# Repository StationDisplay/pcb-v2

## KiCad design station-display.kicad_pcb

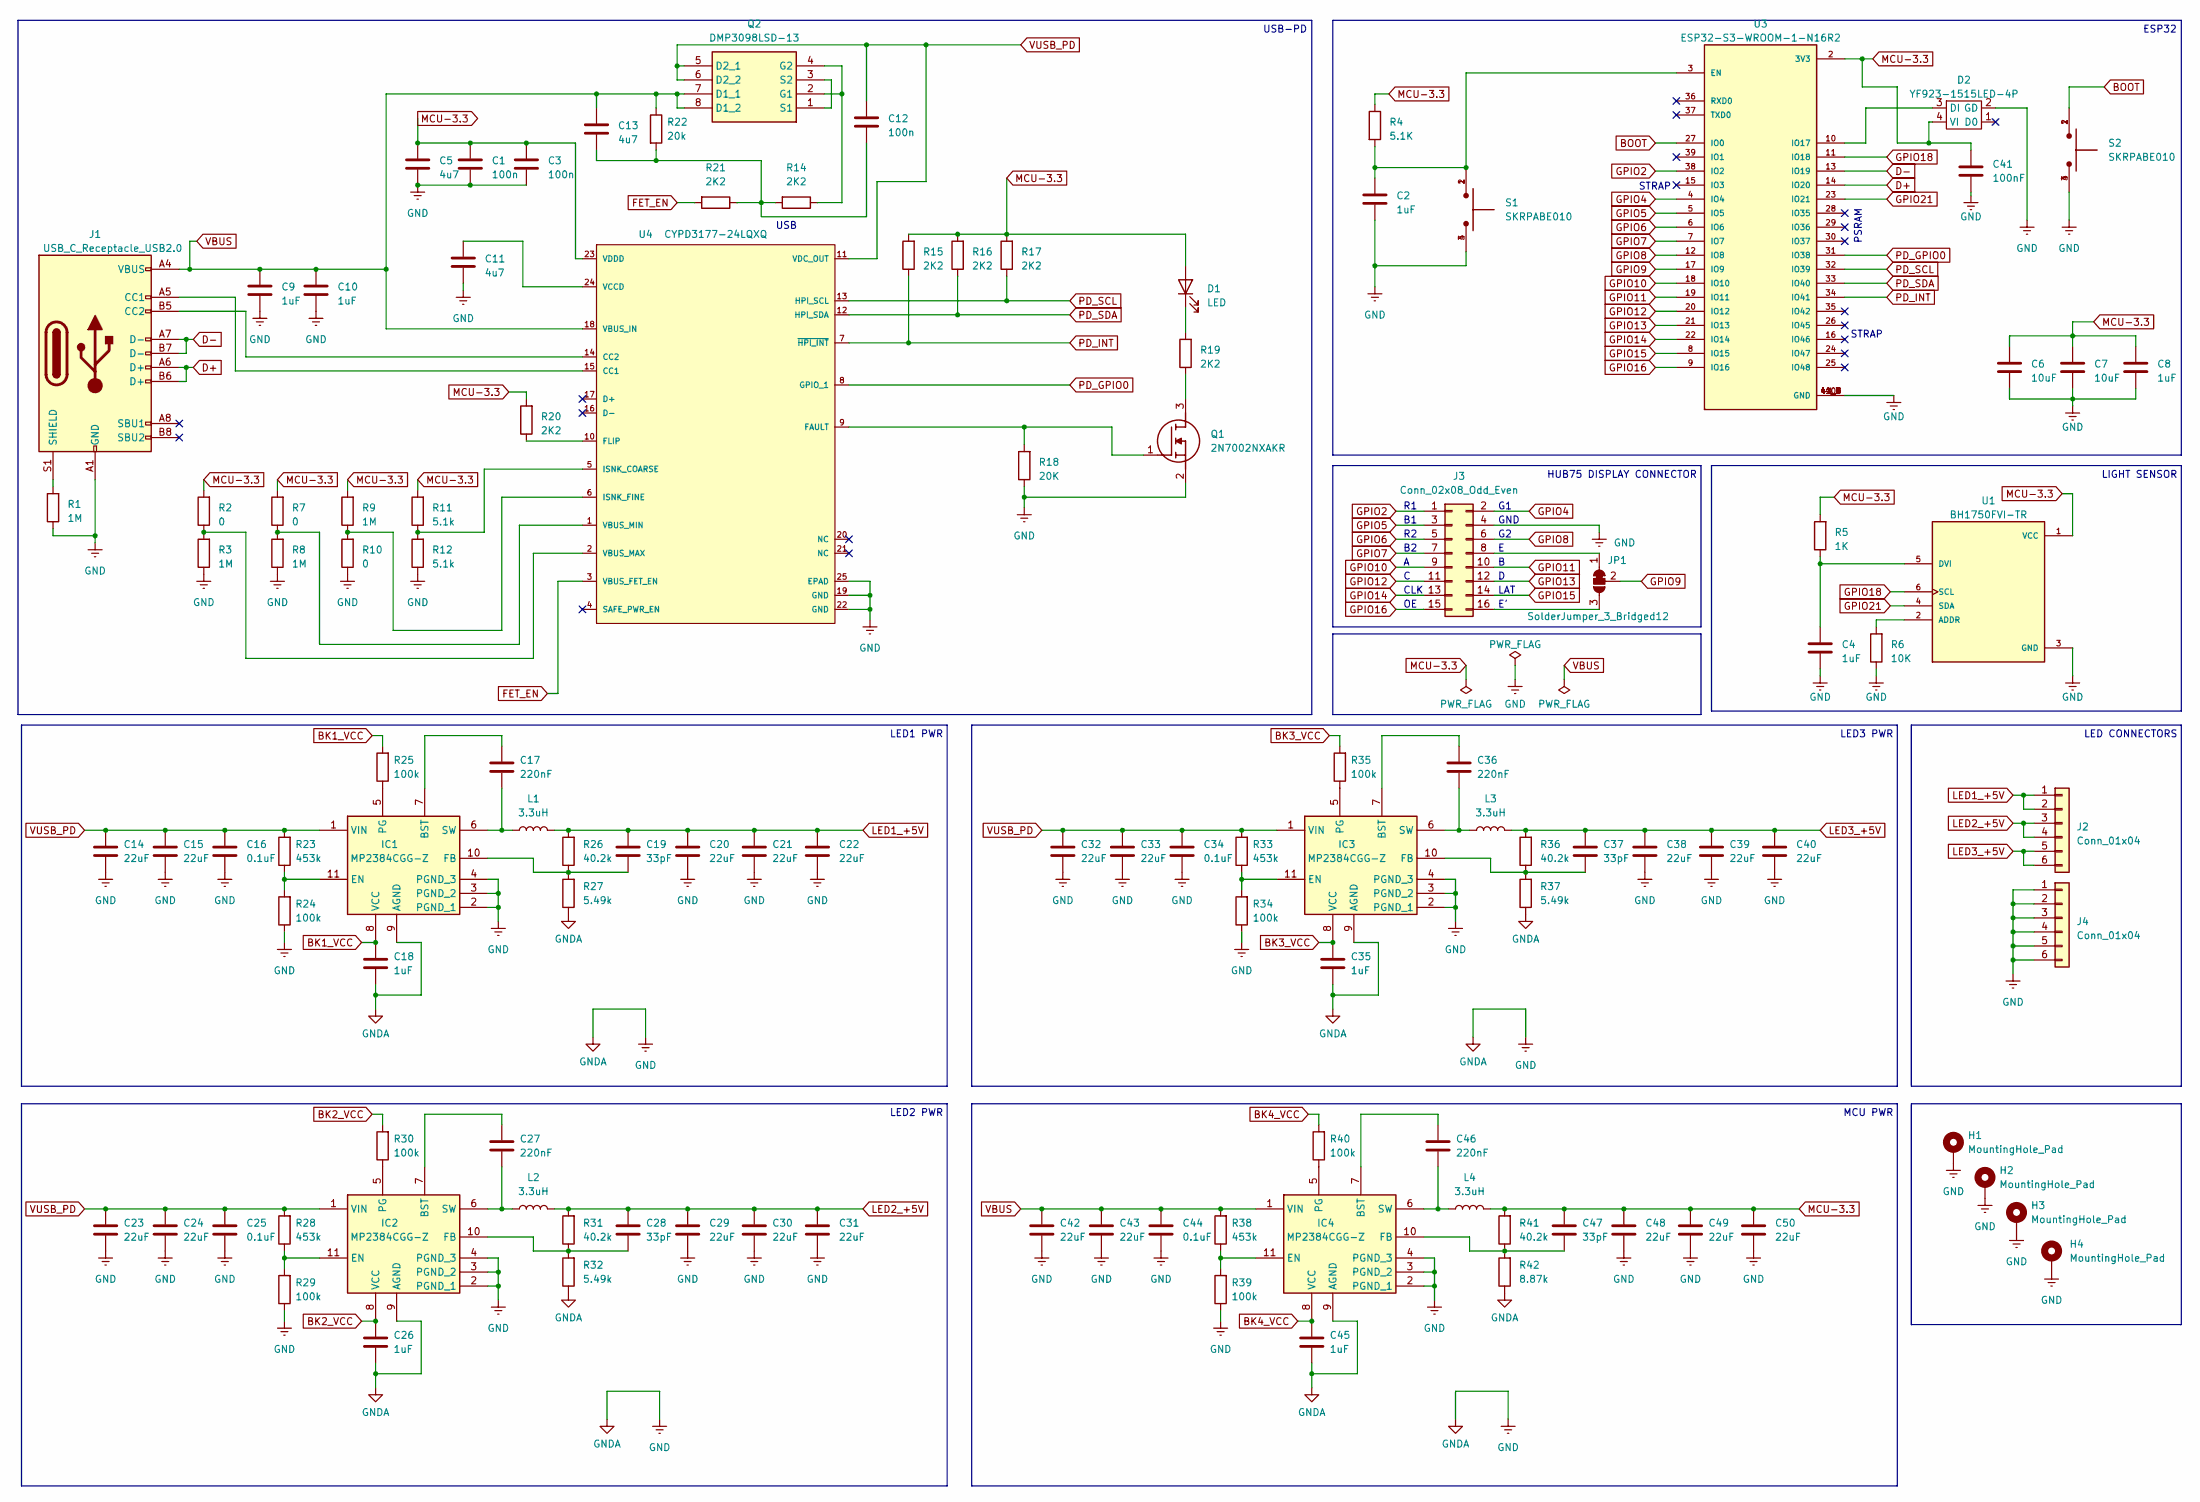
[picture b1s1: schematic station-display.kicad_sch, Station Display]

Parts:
C1, C3, C12: 100n; C_0805_2012Metric
C2, C4, C8, C9, C10: 1uF; C_0805_2012Metric
C5, C11, C13: 4u7; C_0805_2012Metric
C6, C7: 10uF; C_0805_2012Metric
C14, C15, C20, C21, C22, C23, C24, C29, C30, C31, C32, C33, C38, C39, C40, C42, C43, C48, C49, C50: 22uF; C_0805_2012Metric
C16, C25, C34, C44: 0.1uF; C_0805_2012Metric
C17, C27, C36, C46: 220nF; C_0201_0603Metric
C18, C26, C35, C45: 1uF; C_0402_1005Metric
C19, C28, C37, C47: 33pF; C_0805_2012Metric
C41: 100nF; C_0805_2012Metric
D1: LED; LED_0402_1005Metric
D2: YF923-1515LED-4P; LED_SK6812_EC15_1.5x1.5mm; LCSC C5349954
H1, H2, H3, H4: MountingHole_Pad; MountingHole_3.2mm_M3_DIN965_Pad
IC1, IC2, IC3, IC4: MP2384CGG-Z; MP2384CGGZ; Mouser Part Number 946-MP2384CGG-Z
J1: USB_C_Receptacle_USB2.0; TYPE-C-31-M-14; LCSC C223907
J2, J4: Conn_01x04; JST_VH_B6P-VH-B_1x06_P3.96mm_Vertical; LCSC C160314
J3: Conn_02x08_Odd_Even; IDC-Header_2x08_P2.54mm_Vertical_SMD; LCSC C601969
JP1: SolderJumper_3_Bridged12; SolderJumper-3_P1.3mm_Bridged12_RoundedPad1.0x1.5mm
L1, L2, L3, L4: 3.3uH; L_Sunlord_MWSA0605S
Q1: 2N7002NXAKR; SOT95P230X110-3N; Mouser Part Number 771-2N7002NXAKR
Q2: DMP3098LSD-13; SOIC127P600X175-8N; Mouser Part Number 621-DMP3098LSD-13
R1, R3, R8, R9: 1M; R_0402_1005Metric
R2, R7, R10: 0; R_0402_1005Metric
R4: 5.1K; R_0402_1005Metric
R5: 1K; R_0402_1005Metric
R6: 10K; R_0402_1005Metric
R11, R12: 5.1k; R_0402_1005Metric
R14, R15, R16, R17, R19, R20, R21: 2K2; R_0402_1005Metric
R18: 20K; R_0402_1005Metric
R22: 20k; R_0402_1005Metric
R23, R28, R33, R38: 453k; R_0402_1005Metric
R24, R25, R29, R30, R34, R35, R39, R40: 100k; R_0402_1005Metric
R26, R31, R36, R41: 40.2k; R_0402_1005Metric
R27, R32, R37: 5.49k; R_0402_1005Metric
R42: 8.87k; R_0402_1005Metric
S1, S2: SKRPABE010; SW_SKRPABE010
U1: BH1750FVI-TR; XDCR_BH1750FVI-TR; PARTREV D; LCSC C78960
U3: ESP32-S3-WROOM-1-N16R2; XCVR_ESP32-S3-WROOM-1-N16R2; PARTREV v1.0; LCSC C2913198
U4: CYPD3177-24LQXQ; Cypress_Semiconductor-002-16934-0-C-IPC_C; mouser part number 727-CYPD3177-24LQXQ; digikey description IC USB TYPE-C PORT CONTROL 24QFN

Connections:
BK1_VCC: C18.1, IC1.8 (VCC), R25.2
BK2_VCC: C26.1, IC2.8 (VCC), R30.2
BK3_VCC: C35.1, IC3.8 (VCC), R35.2
BK4_VCC: C45.1, IC4.8 (VCC), R40.2
BOOT: S2.1, S2.2, U3.27 (IO0)
D+: J1.A6 (D+), J1.B6 (D+), U3.14 (IO20)
D-: J1.A7 (D-), J1.B7 (D-), U3.13 (IO19)
FET_EN: R21.2, U4.3 (VBUS_FET_EN)
GNDA: C1.2, C2.2, C3.2, C4.2, C5.2, C6.2, C7.2, C8.2, C9.2, C10.2, C11.2, C14.2, C15.2, C16.2, C18.2, C20.2, C21.2, C22.2, C23.2, C24.2, C25.2, C26.2, C29.2, C30.2, C31.2, C32.2, C33.2, C34.2, C35.2, C38.2, C39.2, C40.2, C41.2, C42.2, C43.2, C44.2, C45.2, C48.2, C49.2, C50.2, D2.2 (GD), H1.1, H2.1, H3.1, H4.1, IC1.2 (PGND_1), IC1.3 (PGND_2), IC1.4 (PGND_3), IC1.9 (AGND), IC2.2 (PGND_1), IC2.3 (PGND_2), IC2.4 (PGND_3), IC2.9 (AGND), IC3.2 (PGND_1), IC3.3 (PGND_2), IC3.4 (PGND_3), IC3.9 (AGND), IC4.2 (PGND_1), IC4.3 (PGND_2), IC4.4 (PGND_3), IC4.9 (AGND), J1.A1 (GND), J1.A12 (GND), J1.B1 (GND), J1.B12 (GND), J3.4, J4.1, J4.2, J4.3, J4.4, J4.5, J4.6, Q1.2 (S), R1.1, R3.1, R6.1, R8.1, R10.1, R12.1, R18.1, R24.1, R27.1, R29.1, R32.1, R34.1, R37.1, R39.1, R42.1, S1.3, S1.4, S2.3, S2.4, U1.3 (GND), U3.1 (GND), U3.40 (GND), U3.41_1 (GND), U3.41_2 (GND), U3.41_3 (GND), U3.41_4 (GND), U3.41_5 (GND), U3.41_6 (GND), U3.41_7 (GND), U3.41_8 (GND), U3.41_9 (GND), U4.19 (GND), U4.22 (GND), U4.25 (EPAD)
GPIO2: J3.1, U3.38 (IO2)
GPIO4: J3.2, U3.4 (IO4)
GPIO5: J3.3, U3.5 (IO5)
GPIO6: J3.5, U3.6 (IO6)
GPIO7: J3.7, U3.7 (IO7)
GPIO8: J3.6, U3.12 (IO8)
GPIO9: JP1.2 (C), U3.17 (IO9); also elsewhere on the board
GPIO10: J3.9, U3.18 (IO10)
GPIO11: J3.10, U3.19 (IO11)
GPIO12: J3.11, U3.20 (IO12)
GPIO13: J3.12, U3.21 (IO13)
GPIO14: J3.13, U3.22 (IO14)
GPIO15: J3.14, U3.8 (IO15)
GPIO16: J3.15, U3.9 (IO16)
GPIO18: U1.6 (SCL), U3.11 (IO18)
GPIO21: U1.4 (SDA), U3.23 (IO21)
LED1_+5V: C19.1, C20.1, C21.1, C22.1, J2.1, J2.2, L1.2, R26.2
LED2_+5V: C28.1, C29.1, C30.1, C31.1, J2.3, J2.4, L2.2, R31.2
LED3_+5V: C37.1, C38.1, C39.1, C40.1, J2.5, J2.6, L3.2, R36.2
MCU-3.3: C1.1, C3.1, C5.1, C6.1, C7.1, C8.1, C41.1, C47.1, C48.1, C49.1, C50.1, D1.2 (A), D2.4 (VI), L4.2, R2.2, R4.1, R5.2, R7.2, R9.2, R11.2, R15.2, R16.2, R17.2, R20.2, R41.2, U1.1 (VCC), U3.2 (3V3), U4.23 (VDDD)
unnamed: C12.2, C13.2, R14.2, R21.1, R22.2
unnamed: D1.1 (K), R19.2
unnamed: D2.3 (DI), U3.10 (IO17)
unnamed: C17.1, IC1.7 (BST)
unnamed: IC1.11 (EN), R23.1, R24.2
unnamed: C19.2, IC1.10 (FB), R26.1, R27.2
unnamed: IC1.5 (PG), R25.1
unnamed: C17.2, IC1.6 (SW), L1.1
unnamed: C27.1, IC2.7 (BST)
unnamed: IC2.11 (EN), R28.1, R29.2
unnamed: C28.2, IC2.10 (FB), R31.1, R32.2
unnamed: IC2.5 (PG), R30.1
unnamed: C27.2, IC2.6 (SW), L2.1
unnamed: C36.1, IC3.7 (BST)
unnamed: IC3.11 (EN), R33.1, R34.2
unnamed: C37.2, IC3.10 (FB), R36.1, R37.2
unnamed: IC3.5 (PG), R35.1
unnamed: C36.2, IC3.6 (SW), L3.1
unnamed: C46.1, IC4.7 (BST)
unnamed: IC4.11 (EN), R38.1, R39.2
unnamed: C47.2, IC4.10 (FB), R41.1, R42.2
unnamed: IC4.5 (PG), R40.1
unnamed: C46.2, IC4.6 (SW), L4.1
unnamed: J1.A5 (CC1), U4.15 (CC1)
unnamed: J1.B5 (CC2), U4.14 (CC2)
unnamed: J1.S1 (SHIELD), R1.2
unnamed 55: J3.8, JP1.1 (A); also elsewhere on the board
unnamed 56: J3.16, JP1.3 (B); also elsewhere on the board
unnamed: Q1.3 (D), R19.1
unnamed: Q1.1 (G), R18.2, U4.9 (FAULT)
unnamed: Q2.2 (G1), Q2.4 (G2), R14.1
unnamed: Q2.1 (S1), Q2.3 (S2)
unnamed: R6.2, U1.2 (ADDR)
unnamed: C4.1, R5.1, U1.5 (DVI)
unnamed: C2.1, R4.2, S1.1, S1.2, U3.3 (EN)
unnamed: R20.1, U4.10 (FLIP)
unnamed: R11.1, R12.2, U4.5 (ISNK_COARSE)
unnamed: R9.1, R10.2, U4.6 (ISNK_FINE)
unnamed: R2.1, R3.2, U4.2 (VBUS_MAX)
unnamed: R7.1, R8.2, U4.1 (VBUS_MIN)
unnamed: C11.1, U4.24 (VCCD)
PD_GPIO0: U3.31 (IO38), U4.8 (GPIO_1)
PD_INT: R15.1, U3.34 (IO41), U4.7 (~HPI_INT)
PD_SCL: R17.1, U3.32 (IO39), U4.13 (HPI_SCL)
PD_SDA: R16.1, U3.33 (IO40), U4.12 (HPI_SDA)
VBUS: C9.1, C10.1, C13.1, C42.1, C43.1, C44.1, IC4.1 (VIN), J1.A4 (VBUS), J1.A9 (VBUS), J1.B4 (VBUS), J1.B9 (VBUS), Q2.7 (D1_1), Q2.8 (D1_2), R22.1, R38.2, U4.18 (VBUS_IN)
VUSB_PD: C12.1, C14.1, C15.1, C16.1, C23.1, C24.1, C25.1, C32.1, C33.1, C34.1, IC1.1 (VIN), IC2.1 (VIN), IC3.1 (VIN), Q2.5 (D2_1), Q2.6 (D2_2), R23.2, R28.2, R33.2, U4.11 (VDC_OUT)

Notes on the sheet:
CLK
USB
HUB75 DISPLAY CONNECTOR
MCU PWR
LED1 PWR
STRAP
ESP32
LED CONNECTORS
USB-PD
PSRAM
LED3 PWR
GND
LAT
LIGHT SENSOR
LED2 PWR

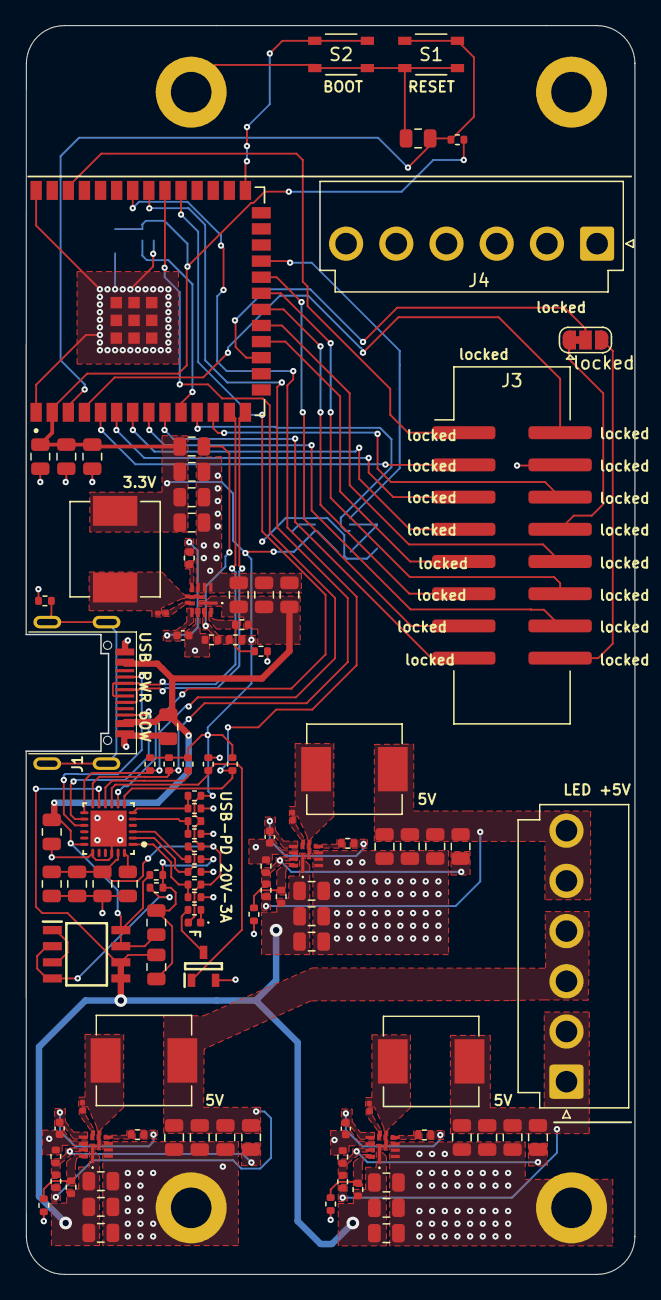
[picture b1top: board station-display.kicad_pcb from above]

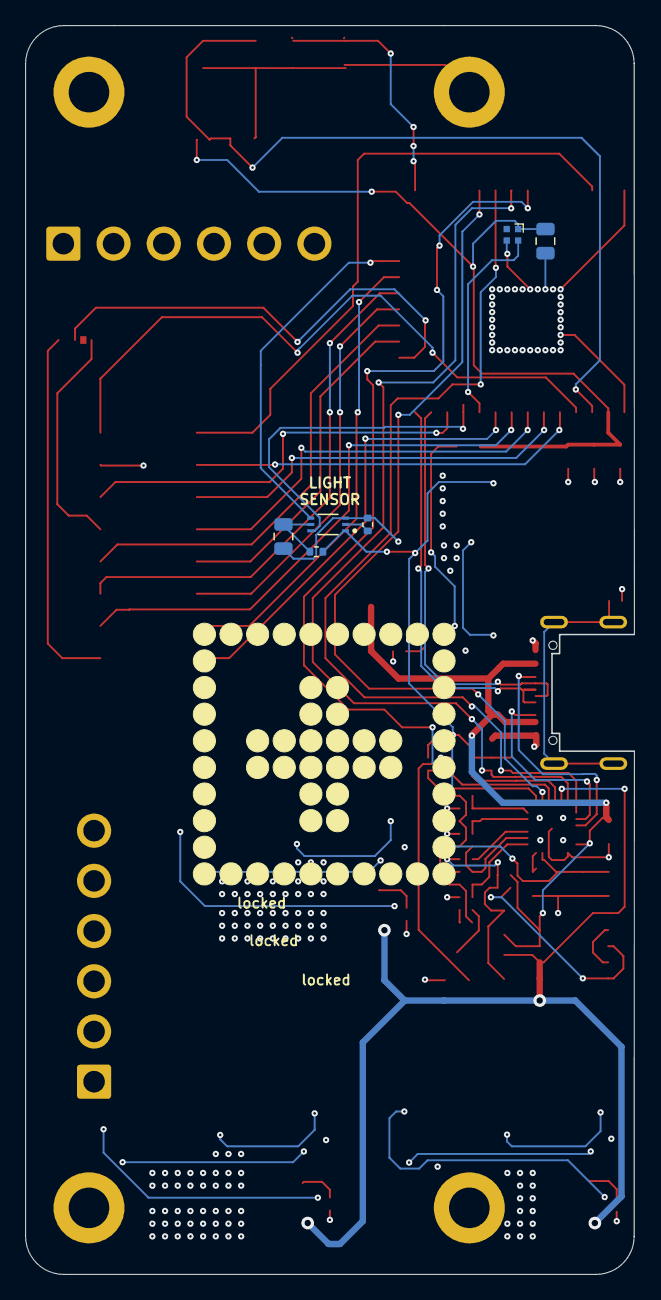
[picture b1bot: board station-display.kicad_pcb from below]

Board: 4 copper layers, 48.0 x 98.5 mm, 117 parts (6 on the bottom side), 76 nets.

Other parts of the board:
locked: SolderJumper_3_Bridged12; SolderJumper-3_P1.3mm_Bridged12_RoundedPad1.0x1.5mm

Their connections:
GPIO9: locked.2 (C); also elsewhere on the board
unnamed 55: locked.1 (A); also elsewhere on the board
unnamed 56: locked.3 (B); also elsewhere on the board

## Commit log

2023-12-03 Init
2023-12-04 added 3d image extention
